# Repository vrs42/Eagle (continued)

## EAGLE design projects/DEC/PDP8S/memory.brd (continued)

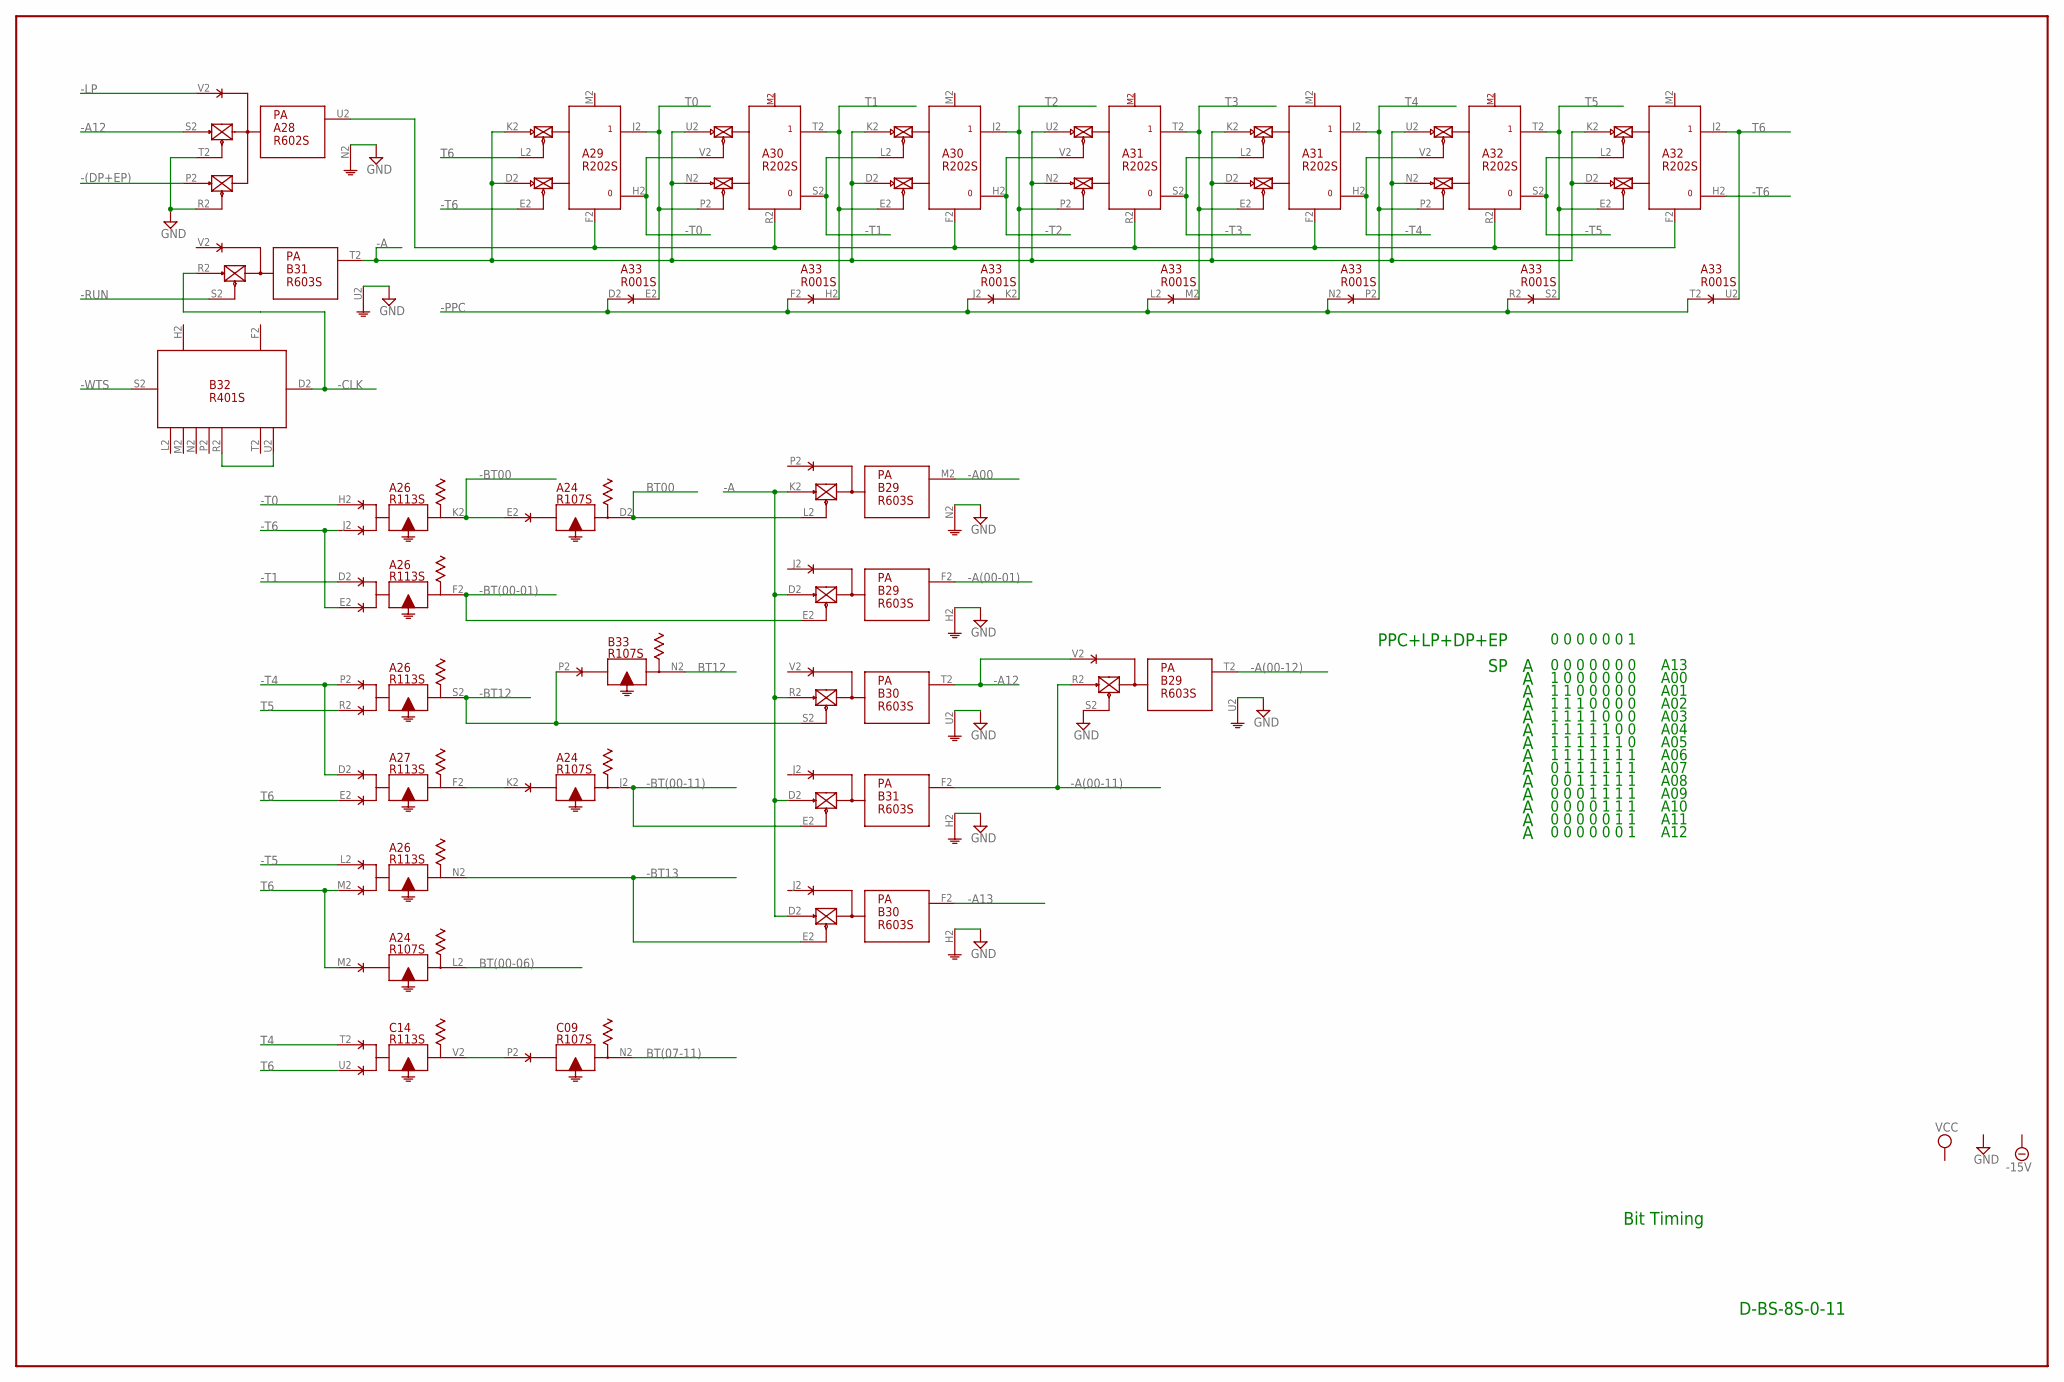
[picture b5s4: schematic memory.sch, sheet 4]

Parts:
A24: R107S; H807S
A26, A27: R113S; H807S
A28: R602S; H807S
A29, A30, A31, A32: R202S; H807S
A33: R001S; H807S
B29, B30, B31: R603S; H807S
B32: R401S; H807S
B33: R107S; H807S
C09: R107S; H807S
C14: R113S; H807S

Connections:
-15V: A24.B2 (-15V), A26.B2 (-15V), A27.B2 (-15V), A28.B2 (-15V), A29.B2 (-15V), A30.B2 (-15V), A31.B2 (-15V), A32.B2 (-15V), A33.B2 (-15V), B29.B2 (-15V), B30.B2 (-15V), B31.B2 (-15V), B32.B2 (-15V), B33.B2 (-15V), C09.B2 (-15V), C14.B2 (-15V); also elsewhere on the board
-(DP+EP): A28.P2 (E); also elsewhere on the board
-A: A29.D2 (PU0), A29.K2 (PU1), A30.D2 (PU0), A30.K2 (PU1), A30.N2 (PU0), A30.U2 (PU1), A31.D2 (PU0), A31.K2 (PU1), A31.N2 (PU0), A31.U2 (PU1), A32.D2 (PU0), A32.K2 (PU1), A32.N2 (PU0), A32.U2 (PU1), B29.D2 (PU0), B29.K2 (PU0), B30.D2 (PU0), B30.R2 (PU0), B31.D2 (PU0), B31.T2 (O); also elsewhere on the board
-A00: B29.M2 (O); also elsewhere on the board
-A12: A28.S2 (H), B29.V2, B30.T2 (O); also elsewhere on the board
-A13: B30.F2 (O); also elsewhere on the board
-A(00-01): B29.F2 (O); also elsewhere on the board
-A(00-11): B29.R2 (PU0), B31.F2 (O); also elsewhere on the board
-A(00-12): B29.T2 (O); also elsewhere on the board
-BT00: A24.E2, A26.K2
-BT12: A26.S2, B30.S2 (EN0), B33.P2; also elsewhere on the board
-BT13: A26.N2, B30.E2 (EN0)
-BT(00-01): A26.F2, B29.E2 (EN0)
-BT(00-11): A24.J2, B31.E2 (EN0)
-CLK: B31.R2 (PU0), B32.D2 (D); also elsewhere on the board
-LP: A28.V2 (L); also elsewhere on the board
-PPC: A33.D2 (D), A33.F2 (D), A33.J2 (D), A33.L2 (D), A33.N2 (D), A33.R2 (D), A33.T2 (D); also elsewhere on the board
-RUN: B31.S2 (EN0); also elsewhere on the board
-T0: A26.H2, A29.H2 (0), A30.V2 (EN1)
-T1: A26.D2, A30.L2 (EN1), A30.S2 (0)
-T2: A30.H2 (0), A31.V2 (EN1)
-T3: A31.L2 (EN1), A31.S2 (0); also elsewhere on the board
-T4: A26.P2, A27.D2, A31.H2 (0), A32.V2 (EN1)
-T5: A26.L2, A32.L2 (EN1), A32.S2 (0)
-T6: A26.E2, A26.J2, A29.E2 (EN0), A32.H2 (0)
-WTS: B32.S2 (S); also elsewhere on the board
BT00: A24.D2, B29.L2 (EN0); also elsewhere on the board
BT12: B33.N2; also elsewhere on the board
BT(00-06): A24.L2; also elsewhere on the board
BT(07-11): C09.N2; also elsewhere on the board
GND: A24.C2 (GND), A26.C2 (GND), A27.C2 (GND), A28.N2 (C), A28.R2 (F), A28.T2 (J), A29.C2 (GND), A30.C2 (GND), A31.C2 (GND), A32.C2 (GND), A33.C2 (GND), B29.C2 (GND), B29.H2 (G), B29.N2 (G), B29.S2 (EN0), B29.U2 (G), B30.C2 (GND), B30.H2 (G), B30.U2 (G), B31.C2 (GND), B31.H2 (G), B31.U2 (G), B32.C2 (GND), B33.C2 (GND), C09.C2 (GND), C14.C2 (GND); also elsewhere on the board
unnamed: A24.K2, A27.F2
unnamed: C09.P2, C14.V2
unnamed: B32.R2 (R), B32.U2 (U)
unnamed: A28.U2 (K), A29.F2 (RESET), A30.F2 (RESET), A30.R2 (RESET), A31.F2 (RESET), A31.R2 (RESET), A32.F2 (RESET), A32.R2 (RESET)
T0: A29.J2 (1), A30.P2 (EN0), A33.E2 (E)
T1: A30.E2 (EN0), A30.T2 (1), A33.H2 (E)
T2: A30.J2 (1), A31.P2 (EN0), A33.K2 (E)
T3: A31.E2 (EN0), A31.T2 (1), A33.M2 (E)
T4: A31.J2 (1), A32.P2 (EN0), A33.P2 (E), C14.T2; also elsewhere on the board
T5: A26.R2, A32.E2 (EN0), A32.T2 (1), A33.S2 (E)
T6: A24.M2, A26.M2, A27.E2, A29.L2 (EN1), A32.J2 (1), A33.U2 (E), C14.U2
VCC: A24.A2 (VCC), A26.A2 (VCC), A27.A2 (VCC), A28.A2 (VCC), A29.A2 (VCC), A30.A2 (VCC), A31.A2 (VCC), A32.A2 (VCC), A33.A2 (VCC), B29.A2 (VCC), B30.A2 (VCC), B31.A2 (VCC), B32.A2 (VCC), B33.A2 (VCC), C09.A2 (VCC), C14.A2 (VCC); also elsewhere on the board

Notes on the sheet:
PPC+LP+DP+EP
A00
A13
A01
A02
A03
A04
A05
A06
A07
A08
A09
A10
A11
A12
D-BS-8S-0-11
Bit Timing

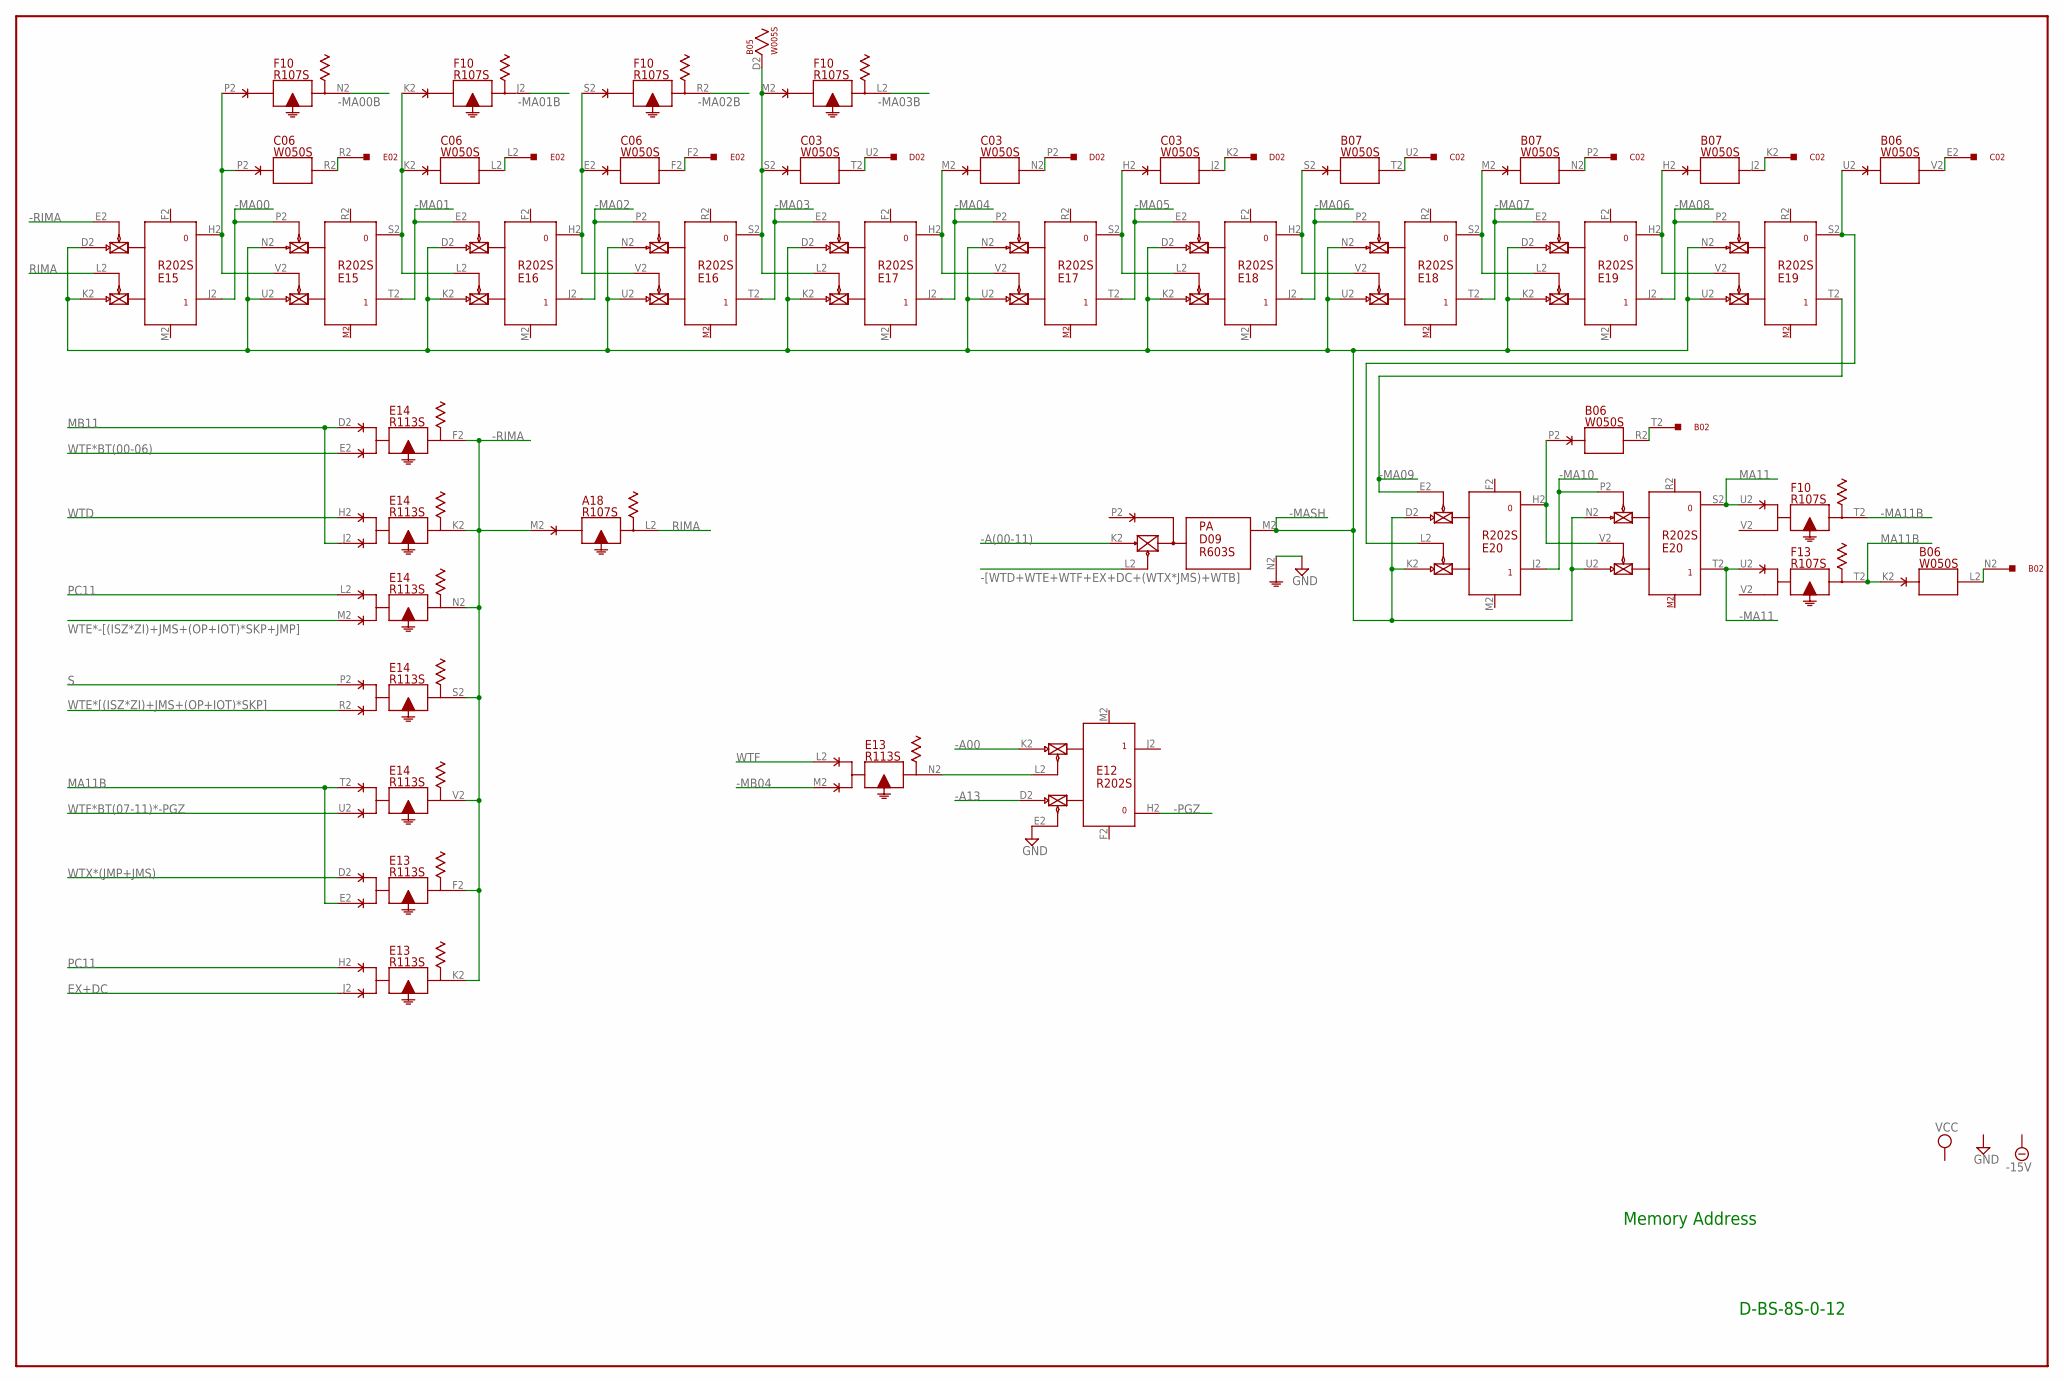
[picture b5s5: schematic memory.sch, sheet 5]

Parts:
A18: R107S; H807S
B02: W023S; H807S
B05: W005S; H807S
B06, B07: W050S; H807S
C02: W023S; H807S
C03, C06: W050S; H807S
D02: W023S; H807S
D09: R603S; H807S
E02: W023S; H807S
E12, E15, E16, E17, E18, E19, E20: R202S; H807S
E13, E14: R113S; H807S
F10, F13: R107S; H807S

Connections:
-15V: A18.B2 (-15V), B05.B2 (-15V), B06.B2 (-15V), B07.B2 (-15V), C03.B2 (-15V), C06.B2 (-15V), D09.B2 (-15V), E12.B2 (-15V), E13.B2 (-15V), E14.B2 (-15V), E15.B2 (-15V), E16.B2 (-15V), E17.B2 (-15V), E18.B2 (-15V), E19.B2 (-15V), E20.B2 (-15V), F10.B2 (-15V), F13.B2 (-15V); also elsewhere on the board
-A00: E12.K2 (PU1); also elsewhere on the board
-A13: E12.D2 (PU0); also elsewhere on the board
-A(00-11): D09.K2 (PU0); also elsewhere on the board
-MA00: E15.J2 (1), E15.P2 (EN0); also elsewhere on the board
-MA00B: F10.N2; also elsewhere on the board
-MA01: E15.T2 (1), E16.E2 (EN0); also elsewhere on the board
-MA01B: F10.J2; also elsewhere on the board
-MA02: E16.J2 (1), E16.P2 (EN0); also elsewhere on the board
-MA02B: F10.R2; also elsewhere on the board
-MA03: E16.T2 (1), E17.E2 (EN0); also elsewhere on the board
-MA03B: F10.L2; also elsewhere on the board
-MA04: E17.J2 (1), E17.P2 (EN0); also elsewhere on the board
-MA05: E17.T2 (1), E18.E2 (EN0); also elsewhere on the board
-MA06: E18.J2 (1), E18.P2 (EN0); also elsewhere on the board
-MA07: E18.T2 (1), E19.E2 (EN0); also elsewhere on the board
-MA08: E19.J2 (1), E19.P2 (EN0); also elsewhere on the board
-MA09: E19.T2 (1), E20.E2 (EN0); also elsewhere on the board
-MA10: E20.J2 (1), E20.P2 (EN0); also elsewhere on the board
-MA11: E20.T2 (1), F13.U2; also elsewhere on the board
-MA11B: F10.T2
-MASH: D09.M2 (O), E15.D2 (PU0), E15.K2 (PU1), E15.N2 (PU0), E15.U2 (PU1), E16.D2 (PU0), E16.K2 (PU1), E16.N2 (PU0), E16.U2 (PU1), E17.D2 (PU0), E17.K2 (PU1), E17.N2 (PU0), E17.U2 (PU1), E18.D2 (PU0), E18.K2 (PU1), E18.N2 (PU0), E18.U2 (PU1), E19.D2 (PU0), E19.K2 (PU1), E19.N2 (PU0), E19.U2 (PU1), E20.D2 (PU0), E20.K2 (PU1), E20.N2 (PU0), E20.U2 (PU1)
-MB04: E13.M2; also elsewhere on the board
-PGZ: E12.H2 (0); also elsewhere on the board
-RIMA: A18.M2, E13.F2, E13.K2, E14.F2, E14.K2, E14.N2, E14.S2, E14.V2, E15.E2 (EN0)
-[WTD+WTE+WTF+EX+DC+(WTX*JMS)+WTB]: D09.L2 (EN0); also elsewhere on the board
EX+DC: E13.J2; also elsewhere on the board
GND: A18.C2 (GND), B05.C2 (GND), B06.C2 (GND), B07.C2 (GND), C03.C2 (GND), C06.C2 (GND), D09.C2 (GND), D09.N2 (G), E12.C2 (GND), E12.E2 (EN0), E13.C2 (GND), E14.C2 (GND), E15.C2 (GND), E16.C2 (GND), E17.C2 (GND), E18.C2 (GND), E19.C2 (GND), E20.C2 (GND), F10.C2 (GND), F13.C2 (GND); also elsewhere on the board
MA11: E20.S2 (0), F10.U2
MA11B: B06.K2, E13.E2, E14.T2, F13.T2; also elsewhere on the board
MB11: E14.D2, E14.J2; also elsewhere on the board
unnamed: C06.P2, E15.H2 (0), E15.V2 (EN1), F10.P2
unnamed: E12.L2 (EN1), E13.N2
unnamed: C06.K2, E15.S2 (0), E16.L2 (EN1), F10.K2
unnamed: C06.E2, E16.H2 (0), E16.V2 (EN1), F10.S2
unnamed: B05.D2, C03.S2, E16.S2 (0), E17.L2 (EN1), F10.M2
unnamed: C03.M2, E17.H2 (0), E17.V2 (EN1)
unnamed: C03.H2, E17.S2 (0), E18.L2 (EN1)
unnamed: B07.S2, E18.H2 (0), E18.V2 (EN1)
unnamed: C06.R2, E02.R2
unnamed: C06.L2, E02.L2
unnamed: C06.F2, E02.F2
unnamed: B07.M2, E18.S2 (0), E19.L2 (EN1)
unnamed: C03.T2, D02.U2
unnamed: B07.H2, E19.H2 (0), E19.V2 (EN1)
unnamed: B06.U2, E19.S2 (0), E20.L2 (EN1)
unnamed: C03.N2, D02.P2
unnamed: B06.P2, E20.H2 (0), E20.V2 (EN1)
unnamed: C03.J2, D02.K2
unnamed: B07.T2, C02.U2
unnamed: B07.N2, C02.P2
unnamed: B07.J2, C02.K2
unnamed: B06.V2, C02.E2
unnamed: B02.T2, B06.R2
unnamed: B02.N2, B06.L2
PC11: E13.H2, E14.L2; also elsewhere on the board
RIMA: A18.L2, E15.L2 (EN1)
S: E14.P2; also elsewhere on the board
VCC: A18.A2 (VCC), B05.A2 (VCC), B06.A2 (VCC), B07.A2 (VCC), C03.A2 (VCC), C06.A2 (VCC), D09.A2 (VCC), E12.A2 (VCC), E13.A2 (VCC), E14.A2 (VCC), E15.A2 (VCC), E16.A2 (VCC), E17.A2 (VCC), E18.A2 (VCC), E19.A2 (VCC), E20.A2 (VCC), F10.A2 (VCC), F13.A2 (VCC); also elsewhere on the board
WTD: E14.H2; also elsewhere on the board
WTE*-[(ISZ*ZI)+JMS+(OP+IOT)*SKP+JMP]: E14.M2; also elsewhere on the board
WTE*[(ISZ*ZI)+JMS+(OP+IOT)*SKP]: E14.R2; also elsewhere on the board
WTF: E13.L2; also elsewhere on the board
WTF*BT(00-06): E14.E2; also elsewhere on the board
WTF*BT(07-11)*-PGZ: E14.U2; also elsewhere on the board
WTX*(JMP+JMS): E13.D2; also elsewhere on the board

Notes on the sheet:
D-BS-8S-0-12
Memory Address

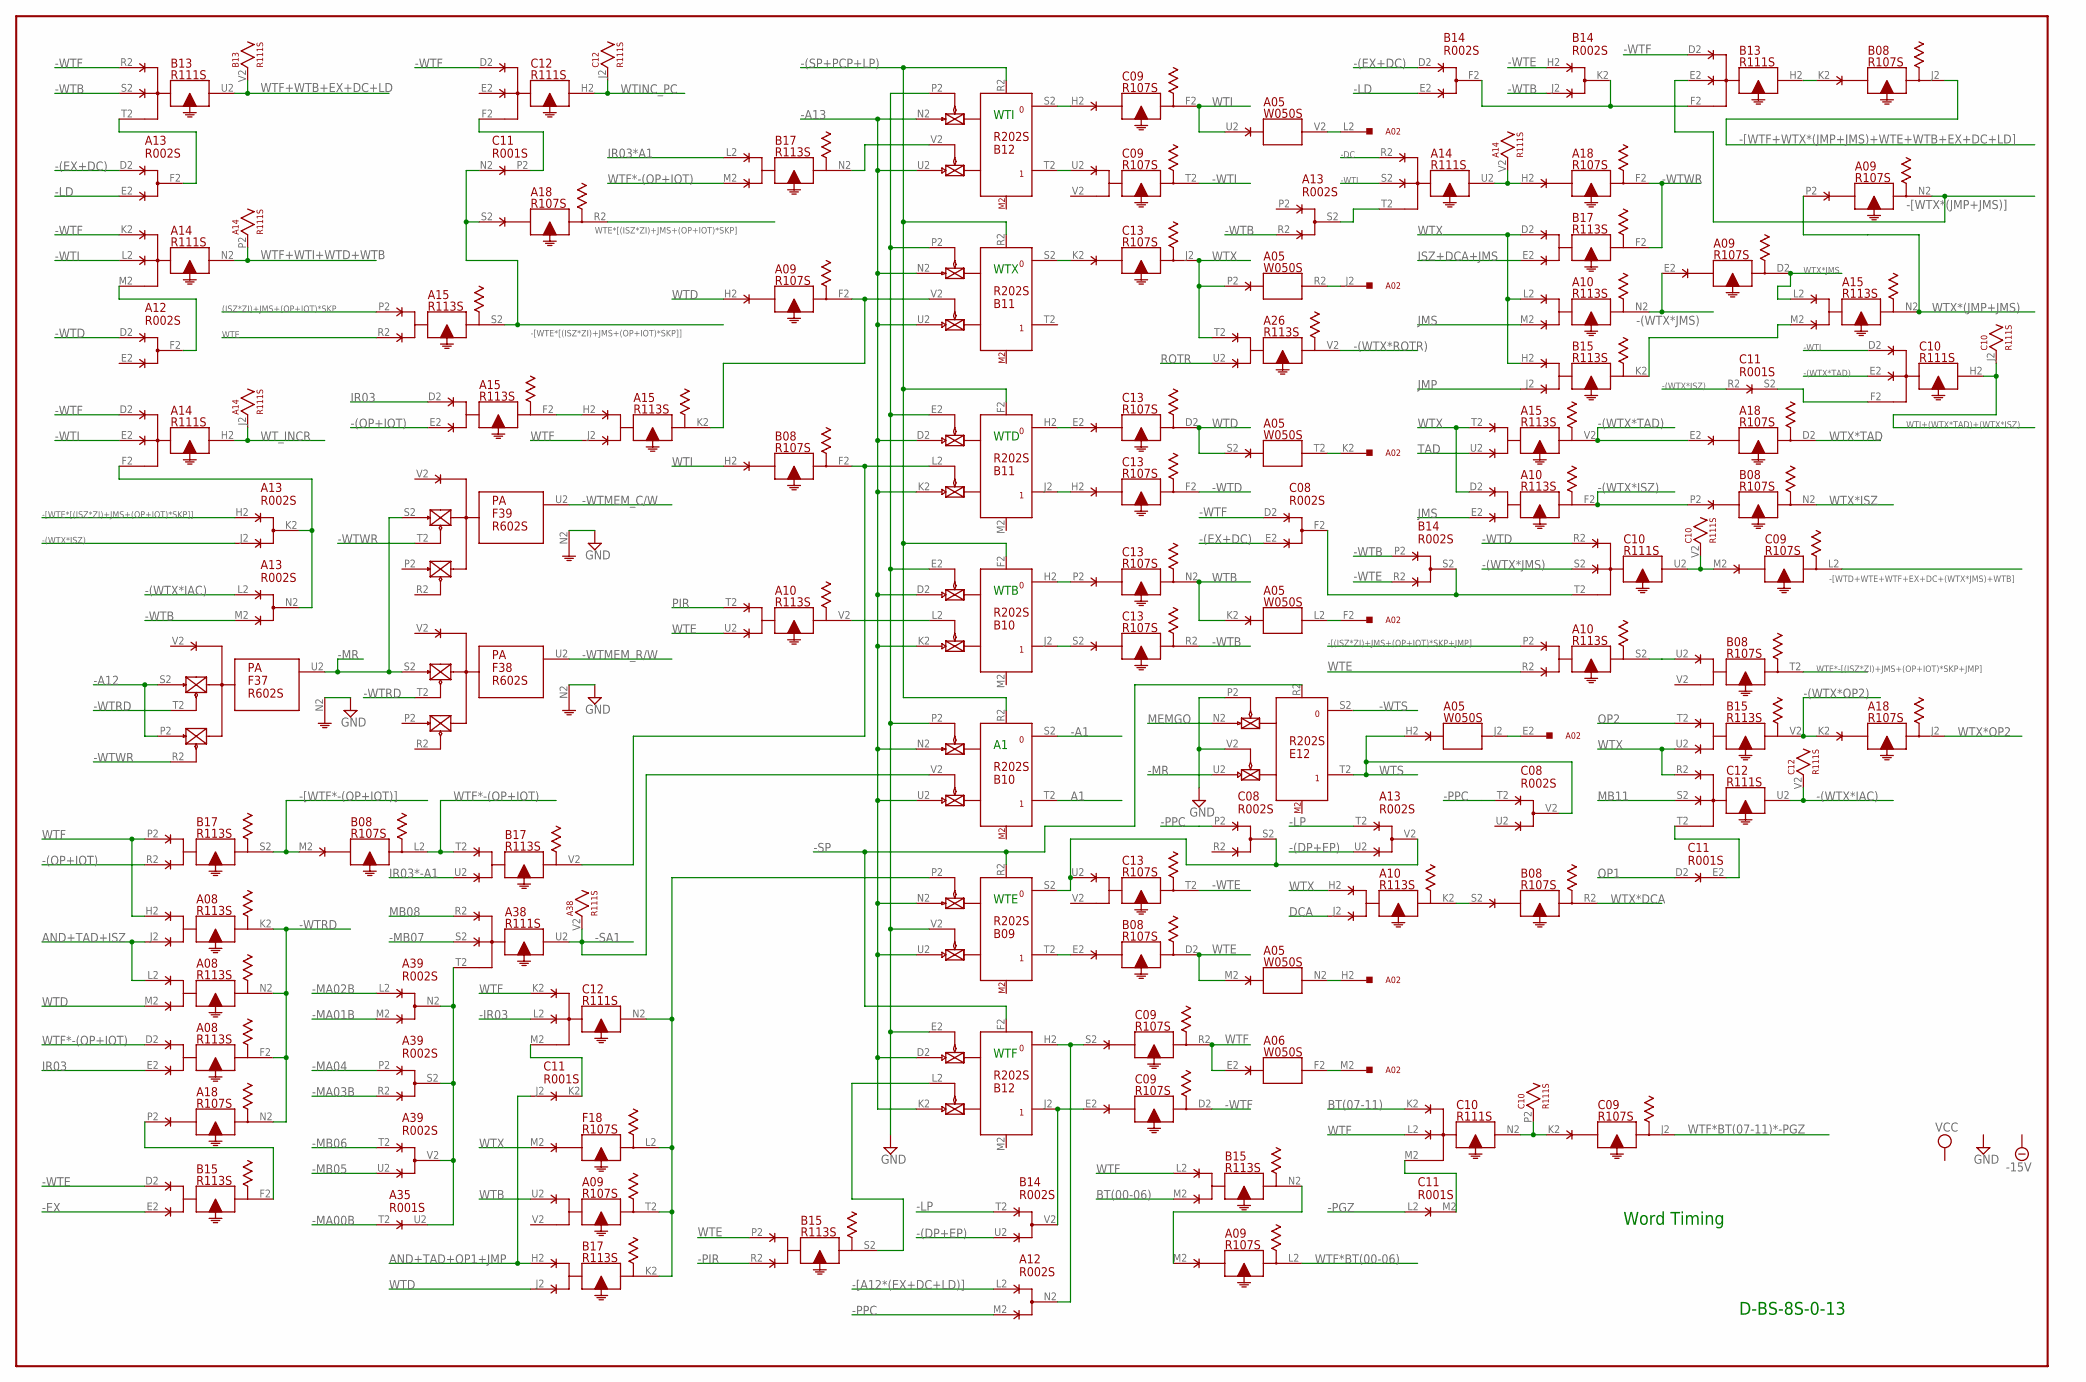
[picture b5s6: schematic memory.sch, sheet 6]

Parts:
A02: W023S; H807S
A05, A06: W050S; H807S
A08, A10, A15, A26: R113S; H807S
A09, A18: R107S; H807S
A12, A13, A39: R002S; H807S
A14, A38: R111S; H807S
A35: R001S; H807S
B08: R107S; H807S
B09, B10, B11, B12: R202S; H807S
B13: R111S; H807S
B14: R002S; H807S
B15, B17: R113S; H807S
C08: R002S; H807S
C09, C13: R107S; H807S
C10, C12: R111S; H807S
C11: R001S; H807S
E12: R202S; H807S
F18: R107S; H807S
F37, F38, F39: R602S; H807S

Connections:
(ISZ*ZI)+JMS+(OP+IOT)*SKP: A15.P2; also elsewhere on the board
-15V: A05.B2 (-15V), A06.B2 (-15V), A08.B2 (-15V), A09.B2 (-15V), A10.B2 (-15V), A12.B2 (-15V), A13.B2 (-15V), A14.B2 (-15V), A15.B2 (-15V), A18.B2 (-15V), A26.B2 (-15V), A35.B2 (-15V), A38.B2 (-15V), A39.B2 (-15V), B08.B2 (-15V), B09.B2 (-15V), B10.B2 (-15V), B11.B2 (-15V), B12.B2 (-15V), B13.B2 (-15V), B14.B2 (-15V), B15.B2 (-15V), B17.B2 (-15V), C08.B2 (-15V), C09.B2 (-15V), C10.B2 (-15V), C11.B2 (-15V), C12.B2 (-15V), C13.B2 (-15V), E12.B2 (-15V), F18.B2 (-15V), F37.B2 (-15V), F38.B2 (-15V), F39.B2 (-15V); also elsewhere on the board
-(DP+EP): A13.U2 (E), B14.U2 (E); also elsewhere on the board
-(EX+DC): A13.D2 (D), B14.D2 (D), C08.E2 (E); also elsewhere on the board
-(OP+IOT): A15.E2, B17.R2; also elsewhere on the board
-(SP+PCP+LP): B10.F2 (RESET), B10.R2 (RESET), B11.F2 (RESET), B11.R2 (RESET), B12.R2 (RESET); also elsewhere on the board
-(WTX*IAC): A13.L2 (D), C12.U2, C12.V2
-(WTX*ISZ): A10.F2, A13.J2 (E), B08.P2, C11.R2 (D); also elsewhere on the board
-(WTX*JMS): A09.E2, A10.N2, C10.S2
-(WTX*OP2): A18.K2, B15.V2; also elsewhere on the board
-(WTX*ROTR): A26.V2; also elsewhere on the board
-(WTX*TAD): A15.V2, A18.E2, C10.E2; also elsewhere on the board
-A1: B10.S2 (0); also elsewhere on the board
-A12: F37.P2 (E), F37.S2 (H); also elsewhere on the board
-A13: B09.N2 (PU0), B09.U2 (PU1), B10.D2 (PU0), B10.K2 (PU1), B10.N2 (PU0), B10.U2 (PU1), B11.D2 (PU0), B11.K2 (PU1), B11.N2 (PU0), B11.U2 (PU1), B12.D2 (PU0), B12.K2 (PU1), B12.N2 (PU0), B12.U2 (PU1); also elsewhere on the board
-DC: A14.R2; also elsewhere on the board
-EX: B15.E2; also elsewhere on the board
-IR03: C12.L2; also elsewhere on the board
-LD: A13.E2 (E), B14.E2 (E); also elsewhere on the board
-LP: A13.T2 (D), B14.T2 (D); also elsewhere on the board
-MA00B: A35.T2 (D); also elsewhere on the board
-MA01B: A39.M2 (E); also elsewhere on the board
-MA02B: A39.L2 (D); also elsewhere on the board
-MA03B: A39.R2 (E); also elsewhere on the board
-MA04: A39.P2 (D); also elsewhere on the board
-MB05: A39.U2 (E); also elsewhere on the board
-MB06: A39.T2 (D); also elsewhere on the board
-MB07: A38.S2; also elsewhere on the board
-MR: E12.U2 (PU1), F37.U2 (K), F38.S2 (H), F39.S2 (H)
-PGZ: C11.L2 (D); also elsewhere on the board
-PIR: B15.R2; also elsewhere on the board
-PPC: A12.M2 (E), C08.P2 (D), C08.T2 (D); also elsewhere on the board
-SA1: A38.U2, A38.V2, B10.V2 (EN1)
-SP: B09.R2 (RESET), B12.F2 (RESET), E12.R2 (RESET); also elsewhere on the board
-WTB: A13.M2 (E), A13.R2 (E), B13.S2, B14.J2 (E), B14.P2 (D), C13.R2; also elsewhere on the board
-WTD: A12.D2 (D), C10.R2, C13.F2; also elsewhere on the board
-WTE: B14.H2 (D), B14.R2 (E), B15.D2, C13.T2; also elsewhere on the board
-WTF: A14.D2, A14.K2, B13.D2, B13.R2, C08.D2 (D), C09.D2, C12.D2; also elsewhere on the board
-WTI: A14.E2, A14.L2, A14.S2, C09.T2, C10.D2
-WTMEM_C/W: F39.U2 (K); also elsewhere on the board
-WTMEM_R/W: F38.U2 (K); also elsewhere on the board
-WTRD: A08.F2, A08.K2, A08.N2, A18.N2, F37.T2 (J), F38.T2 (J)
-WTS: E12.S2 (0); also elsewhere on the board
-WTWR: A18.F2, B17.F2, F37.R2 (F), F39.T2 (J); also elsewhere on the board
-[(ISZ*ZI)+JMS+(OP+IOT)*SKP+JMP]: A10.P2; also elsewhere on the board
-[A12*(EX+DC+LD)]: A12.L2 (D); also elsewhere on the board
-[WTD+WTE+WTF+EX+DC+(WTX*JMS)+WTB]: C09.L2; also elsewhere on the board
-[WTE*[(ISZ*ZI)+JMS+(OP+IOT)*SKP]]: A13.H2 (D), A15.S2, A18.S2, C11.N2 (D)
-[WTF*-(OP+IOT)]: B08.M2, B17.S2
-[WTF+WTX*(JMP+JMS)+WTE+WTB+EX+DC+LD]: B08.J2; also elsewhere on the board
-[WTX*(JMP+JMS)]: A09.N2, B13.E2; also elsewhere on the board
A1: B10.T2 (1); also elsewhere on the board
AND+TAD+ISZ: A08.J2, A08.L2; also elsewhere on the board
AND+TAD+OP1+JMP: B17.H2, C11.J2 (D); also elsewhere on the board
BT(00-06): B15.M2; also elsewhere on the board
BT(07-11): C10.K2; also elsewhere on the board
DCA: A10.J2; also elsewhere on the board
GND: A05.C2 (GND), A06.C2 (GND), A08.C2 (GND), A09.C2 (GND), A10.C2 (GND), A12.C2 (GND), A13.C2 (GND), A14.C2 (GND), A15.C2 (GND), A18.C2 (GND), A26.C2 (GND), A35.C2 (GND), A38.C2 (GND), A39.C2 (GND), B08.C2 (GND), B09.C2 (GND), B09.V2 (EN1), B10.C2 (GND), B10.E2 (EN0), B10.P2 (EN0), B11.C2 (GND), B11.E2 (EN0), B11.P2 (EN0), B12.C2 (GND), B12.E2 (EN0), B12.P2 (EN0), B13.C2 (GND), B14.C2 (GND), B15.C2 (GND), B17.C2 (GND), C08.C2 (GND), C09.C2 (GND), C10.C2 (GND), C11.C2 (GND), C12.C2 (GND), C13.C2 (GND), E12.C2 (GND), E12.P2 (EN0), E12.V2 (EN1), F18.C2 (GND), F37.N2 (C), F38.N2 (C), F39.N2 (C); also elsewhere on the board
IR03: A08.E2, A15.D2; also elsewhere on the board
IR03*-A1: B17.U2; also elsewhere on the board
IR03*A1: B17.L2; also elsewhere on the board
ISZ+DCA+JMS: B17.E2; also elsewhere on the board
JMP: B15.J2; also elsewhere on the board
JMS: A10.E2, A10.M2; also elsewhere on the board
MB08: A38.R2; also elsewhere on the board
MB11: C12.S2; also elsewhere on the board
MEMGO: E12.N2 (PU0); also elsewhere on the board
unnamed: A13.F2 (F), B13.T2
unnamed: C11.P2 (E), C12.F2
unnamed: A13.K2 (F), A13.N2 (F), A14.F2
unnamed: A15.F2, A15.H2
unnamed: A12.F2 (F), A14.M2
unnamed: A35.U2 (E), A38.T2, A39.N2 (F), A39.S2 (F), A39.V2 (F)
unnamed: C11.K2 (E), C12.M2
unnamed: A18.P2, B15.F2
unnamed: B12.S2 (0), C09.H2
unnamed: B12.T2 (1), C09.U2
unnamed: B11.S2 (0), C13.K2
unnamed: B11.H2 (0), C13.E2
unnamed: B11.J2 (1), C13.H2
unnamed: B10.H2 (0), C13.P2
unnamed: B10.J2 (1), C13.S2
unnamed: B12.J2 (1), B14.V2 (F), C09.E2
unnamed: A09.T2, B09.P2 (EN0), B17.K2, C12.N2, F18.L2
unnamed: A10.V2, B10.L2 (EN1)
unnamed: B08.F2, B11.L2 (EN1), B17.V2
unnamed: A09.F2, A15.K2, B11.V2 (EN1)
unnamed: B12.V2 (EN1), B17.N2
unnamed: B08.E2, B09.T2 (1)
unnamed: A13.V2 (F), B09.S2 (0), C08.S2 (F), C13.U2
unnamed: A12.N2 (F), B12.H2 (0), C09.S2
unnamed: A02.M2, A06.F2
unnamed: A02.H2, A05.N2
unnamed: A02.F2, A05.L2
unnamed: B12.L2 (EN1), B15.S2
unnamed: A02.L2, A05.V2
unnamed: A02.J2, A05.R2
unnamed: A02.K2, A05.T2
unnamed: A14.U2, A14.V2, A18.H2
unnamed: A15.M2, B15.K2
unnamed: A13.S2 (F), A14.T2
unnamed: B08.K2, B13.H2
unnamed: B13.F2, B14.F2 (F), B14.K2 (F)
unnamed: B14.S2 (F), C08.F2 (F), C10.T2
unnamed: C09.M2, C10.U2, C10.V2
unnamed: C10.F2, C11.S2 (E)
unnamed: A02.E2, A05.J2
unnamed: A10.S2, B08.U2
unnamed: A09.M2, B15.N2
unnamed: C10.M2, C11.M2 (E)
unnamed: C09.K2, C10.N2, C10.P2
unnamed: A10.K2, B08.S2
unnamed: C11.E2 (E), C12.T2
OP1: C11.D2 (D); also elsewhere on the board
OP2: B15.T2; also elsewhere on the board
PIR: A10.T2; also elsewhere on the board
ROTR: A26.U2; also elsewhere on the board
TAD: A15.U2; also elsewhere on the board
VCC: A05.A2 (VCC), A06.A2 (VCC), A08.A2 (VCC), A09.A2 (VCC), A10.A2 (VCC), A12.A2 (VCC), A13.A2 (VCC), A14.A2 (VCC), A15.A2 (VCC), A18.A2 (VCC), A26.A2 (VCC), A35.A2 (VCC), A38.A2 (VCC), A39.A2 (VCC), B08.A2 (VCC), B09.A2 (VCC), B10.A2 (VCC), B11.A2 (VCC), B12.A2 (VCC), B13.A2 (VCC), B14.A2 (VCC), B15.A2 (VCC), B17.A2 (VCC), C08.A2 (VCC), C09.A2 (VCC), C10.A2 (VCC), C11.A2 (VCC), C12.A2 (VCC), C13.A2 (VCC), E12.A2 (VCC), F18.A2 (VCC), F37.A2 (VCC), F38.A2 (VCC), F39.A2 (VCC); also elsewhere on the board
WTB: A05.K2, A09.U2, C13.N2; also elsewhere on the board
WTD: A05.S2, A08.M2, A09.H2, B17.J2, C13.D2; also elsewhere on the board
WTE: A05.M2, A10.R2, A10.U2, A15.R2, B08.D2, B15.P2; also elsewhere on the board
WTE*-[(ISZ*ZI)+JMS+(OP+IOT)*SKP+JMP]: B08.T2; also elsewhere on the board
WTE*[(ISZ*ZI)+JMS+(OP+IOT)*SKP]: A18.R2; also elsewhere on the board
WTF: A06.E2, A08.H2, A15.J2, B15.L2, B17.P2, C09.R2, C10.L2, C12.K2; also elsewhere on the board
WTF*-(OP+IOT): A08.D2, B08.L2, B17.M2, B17.T2
WTF*BT(00-06): A09.L2; also elsewhere on the board
WTF*BT(07-11)*-PGZ: C09.J2; also elsewhere on the board
WTF+WTB+EX+DC+LD: B13.U2, B13.V2; also elsewhere on the board
WTF+WTI+WTD+WTB: A14.N2, A14.P2; also elsewhere on the board
WTI: A05.U2, B08.H2, C09.F2; also elsewhere on the board
WTI+(WTX*TAD)+(WTX*ISZ): C10.H2, C10.J2; also elsewhere on the board
WTINC_PC: C12.H2, C12.J2; also elsewhere on the board
WTS: A05.H2, C08.V2 (F), E12.T2 (1); also elsewhere on the board
WTX: A05.P2, A10.D2, A10.H2, A10.L2, A15.T2, A26.T2, B15.H2, B15.U2, B17.D2, C12.R2, C13.J2, F18.M2; also elsewhere on the board
WTX*(JMP+JMS): A09.P2, A15.N2; also elsewhere on the board
WTX*DCA: B08.R2; also elsewhere on the board
WTX*ISZ: B08.N2; also elsewhere on the board
WTX*JMS: A09.D2, A15.L2; also elsewhere on the board
WTX*OP2: A18.J2; also elsewhere on the board
WTX*TAD: A18.D2; also elsewhere on the board
WT_INCR: A14.H2, A14.J2; also elsewhere on the board

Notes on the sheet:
D-BS-8S-0-13
Word Timing
WTI
WTX
WTD
WTB
WTE
WTF
